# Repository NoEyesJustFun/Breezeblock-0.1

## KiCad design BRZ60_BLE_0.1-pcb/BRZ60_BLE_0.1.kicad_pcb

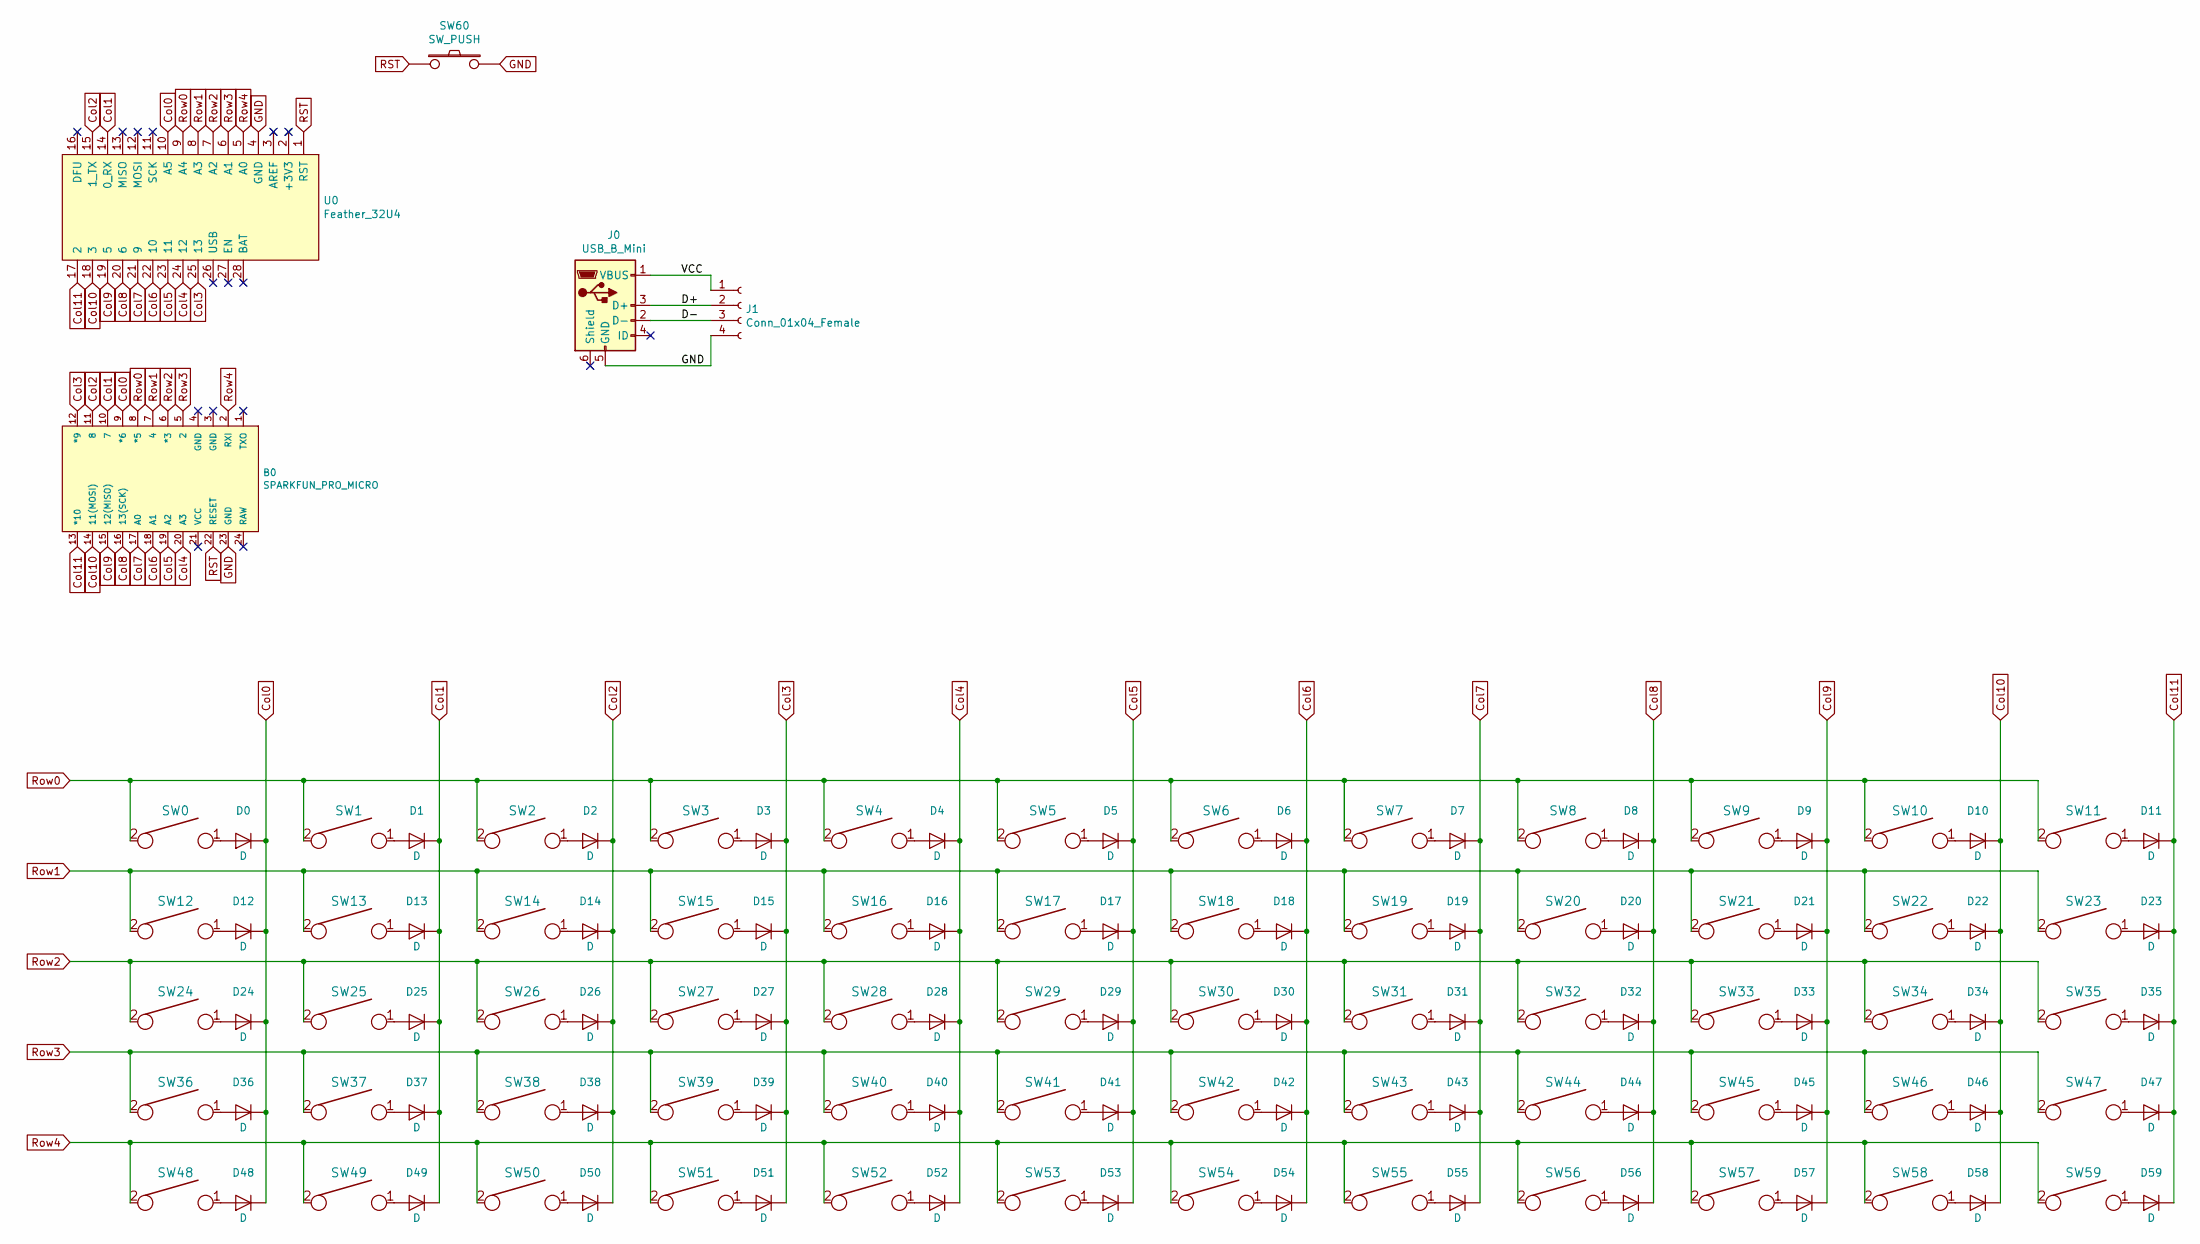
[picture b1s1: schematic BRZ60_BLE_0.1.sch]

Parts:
B0: SPARKFUN_PRO_MICRO; ArduinoProMicro
D0, D1, D2, D3, D4, D5, D6, D7, D8, D9, D10, D11, D12, D13, D14, D15, D16, D17, D18, D19, D20, D21, D22, D23, D24, D25, D26, D27, D28, D29, D30, D31, D32, D33, D34, D35, D36, D37, D38, D39, D40, D41, D42, D43, D44, D45, D46, D47, D48, D49, D50, D51, D52, D53, D54, D55, D56, D57, D58, D59: D; Diode-Hybrid-Back
J0: USB_B_Mini; USB-Mini-B_ LCSC-C46398
J1: Conn_01x04_Female; PinSocket_1x04_P2.00mm_Vertical
SW0, SW1, SW2, SW3, SW4, SW5, SW6, SW7, SW8, SW9, SW10, SW11, SW12, SW13, SW14, SW15, SW16, SW17, SW18, SW19, SW20, SW21, SW22, SW23, SW24, SW25, SW26, SW27, SW28, SW29, SW30, SW31, SW32, SW33, SW34, SW35, SW36, SW37, SW38, SW39, SW40, SW41, SW42, SW43, SW44, SW45, SW46, SW47, SW48, SW49, SW50, SW51, SW52, SW53, SW54, SW55, SW56, SW57, SW58, SW59: KEYSW; MX-Alps-Choc-1U-NoLED
SW60: SW_PUSH; SW_SPST_TL3342
U0: Feather_32U4; PCB_FeatherWing

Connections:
/D+: J0.3 (D+), J1.2
/D-: J0.2 (D-), J1.3
/VCC: J0.1 (VBUS), J1.1
Col0: B0.9 (*6), D0.1 (K), D12.1 (K), D24.1 (K), D36.1 (K), D48.1 (K), U0.10 (A5)
Col1: B0.10 (7), D1.1 (K), D13.1 (K), D25.1 (K), D37.1 (K), D49.1 (K), U0.14 (0_RX)
Col2: B0.11 (8), D2.1 (K), D14.1 (K), D26.1 (K), D38.1 (K), D50.1 (K), U0.15 (1_TX)
Col3: B0.12 (*9), D3.1 (K), D15.1 (K), D27.1 (K), D39.1 (K), D51.1 (K), U0.25 (13)
Col4: B0.20 (A3), D4.1 (K), D16.1 (K), D28.1 (K), D40.1 (K), D52.1 (K), U0.24 (12)
Col5: B0.19 (A2), D5.1 (K), D17.1 (K), D29.1 (K), D41.1 (K), D53.1 (K), U0.23 (11)
Col6: B0.18 (A1), D6.1 (K), D18.1 (K), D30.1 (K), D42.1 (K), D54.1 (K), U0.22 (10)
Col7: B0.17 (A0), D7.1 (K), D19.1 (K), D31.1 (K), D43.1 (K), D55.1 (K), U0.21 (9)
Col8: B0.16 (13(SCK)), D8.1 (K), D20.1 (K), D32.1 (K), D44.1 (K), D56.1 (K), U0.20 (6)
Col9: B0.15 (12(MISO)), D9.1 (K), D21.1 (K), D33.1 (K), D45.1 (K), D57.1 (K), U0.19 (5)
Col10: B0.14 (11(MOSI)), D10.1 (K), D22.1 (K), D34.1 (K), D46.1 (K), D58.1 (K), U0.18 (3)
Col11: B0.13 (*10), D11.1 (K), D23.1 (K), D35.1 (K), D47.1 (K), D59.1 (K), U0.17 (2)
GND: B0.23 (GND), J0.5 (GND), J1.4, SW60.2, U0.4 (GND); also elsewhere on the board
unnamed: D0.2 (A), SW0.1
unnamed: D1.2 (A), SW1.1
unnamed: D2.2 (A), SW2.1
unnamed: D3.2 (A), SW3.1
unnamed: D4.2 (A), SW4.1
unnamed: D5.2 (A), SW5.1
unnamed: D6.2 (A), SW6.1
unnamed: D7.2 (A), SW7.1
unnamed: D8.2 (A), SW8.1
unnamed: D9.2 (A), SW9.1
unnamed: D10.2 (A), SW10.1
unnamed: D11.2 (A), SW11.1
unnamed: D12.2 (A), SW12.1
unnamed: D13.2 (A), SW13.1
unnamed: D14.2 (A), SW14.1
unnamed: D15.2 (A), SW15.1
unnamed: D16.2 (A), SW16.1
unnamed: D17.2 (A), SW17.1
unnamed: D18.2 (A), SW18.1
unnamed: D19.2 (A), SW19.1
unnamed: D20.2 (A), SW20.1
unnamed: D21.2 (A), SW21.1
unnamed: D22.2 (A), SW22.1
unnamed: D23.2 (A), SW23.1
unnamed: D24.2 (A), SW24.1
unnamed: D25.2 (A), SW25.1
unnamed: D26.2 (A), SW26.1
unnamed: D27.2 (A), SW27.1
unnamed: D28.2 (A), SW28.1
unnamed: D29.2 (A), SW29.1
unnamed: D30.2 (A), SW30.1
unnamed: D31.2 (A), SW31.1
unnamed: D32.2 (A), SW32.1
unnamed: D33.2 (A), SW33.1
unnamed: D34.2 (A), SW34.1
unnamed: D35.2 (A), SW35.1
unnamed: D36.2 (A), SW36.1
unnamed: D37.2 (A), SW37.1
unnamed: D38.2 (A), SW38.1
unnamed: D39.2 (A), SW39.1
unnamed: D40.2 (A), SW40.1
unnamed: D41.2 (A), SW41.1
unnamed: D42.2 (A), SW42.1
unnamed: D43.2 (A), SW43.1
unnamed: D44.2 (A), SW44.1
unnamed: D45.2 (A), SW45.1
unnamed: D46.2 (A), SW46.1
unnamed: D47.2 (A), SW47.1
unnamed: D48.2 (A), SW48.1
unnamed: D49.2 (A), SW49.1
unnamed: D50.2 (A), SW50.1
unnamed: D51.2 (A), SW51.1
unnamed 73: D52.2 (A), SW52.1; also elsewhere on the board
unnamed 74: D53.2 (A), SW53.1; also elsewhere on the board
unnamed 75: D54.2 (A), SW54.1; also elsewhere on the board
unnamed: D55.2 (A), SW55.1
unnamed: D56.2 (A), SW56.1
unnamed: D57.2 (A), SW57.1
unnamed: D58.2 (A), SW58.1
unnamed: D59.2 (A), SW59.1
RST: B0.22 (RESET), SW60.1, U0.1 (RST); also elsewhere on the board
Row0: B0.8 (*5), SW0.2, SW1.2, SW2.2, SW3.2, SW4.2, SW5.2, SW6.2, SW7.2, SW8.2, SW9.2, SW10.2, SW11.2, U0.9 (A4)
Row1: B0.7 (4), SW12.2, SW13.2, SW14.2, SW15.2, SW16.2, SW17.2, SW18.2, SW19.2, SW20.2, SW21.2, SW22.2, SW23.2, U0.8 (A3)
Row2: B0.6 (*3), SW24.2, SW25.2, SW26.2, SW27.2, SW28.2, SW29.2, SW30.2, SW31.2, SW32.2, SW33.2, SW34.2, SW35.2, U0.7 (A2)
Row3: B0.5 (2), SW36.2, SW37.2, SW38.2, SW39.2, SW40.2, SW41.2, SW42.2, SW43.2, SW44.2, SW45.2, SW46.2, SW47.2, U0.6 (A1)
Row4: B0.2 (RXI), SW48.2, SW49.2, SW50.2, SW51.2, SW52.2, SW53.2, SW54.2, SW55.2, SW56.2, SW57.2, SW58.2, SW59.2, U0.5 (A0); also elsewhere on the board

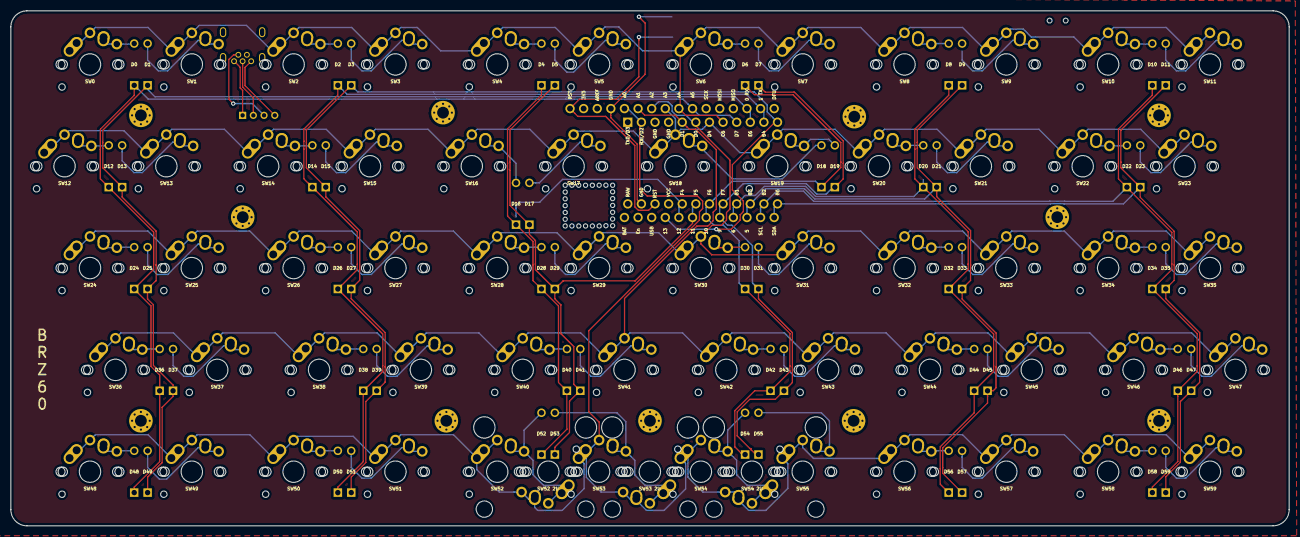
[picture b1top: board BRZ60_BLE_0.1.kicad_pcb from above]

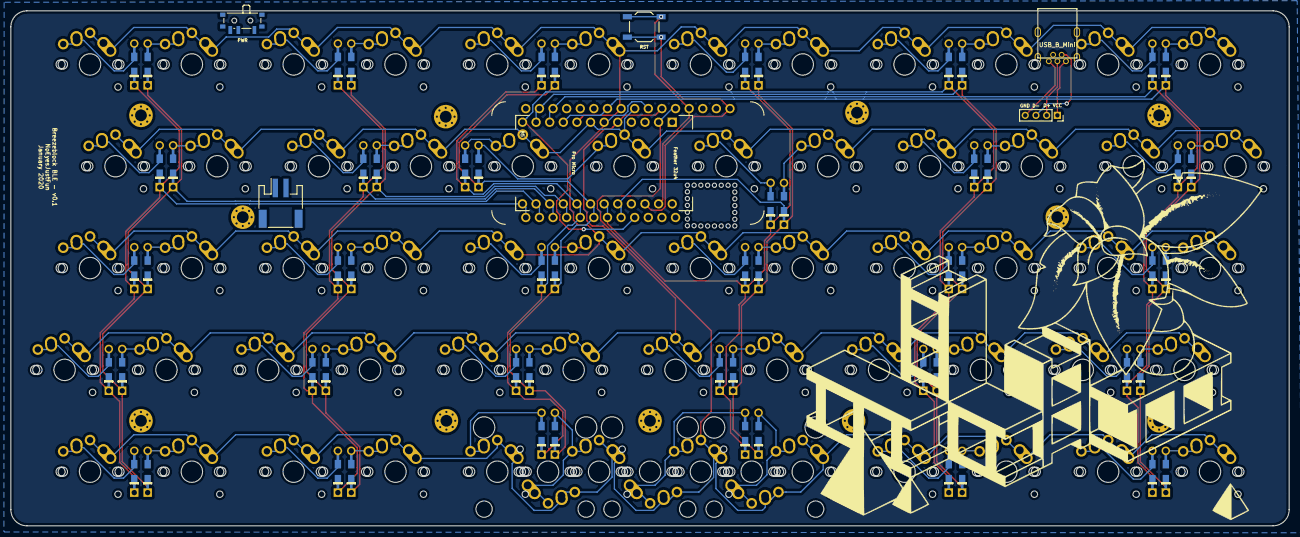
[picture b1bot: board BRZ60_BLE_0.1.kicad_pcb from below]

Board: 2 copper layers, 238.6 x 96.1 mm, 130 parts (7 on the bottom side), 82 nets.

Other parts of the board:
LiPo Conn: JST_PH_S2B-PH-SM4-TB_02x2.00mm_Angled
PWR: SW_SPDT_PCM12
RST: SW_PUSH; SW_SPST_TL3342
SW52#2: KEYSW; MX-Alps-Choc-1U-NoLED
SW53 2U, SW54 2U: KEYSW; MX-Alps-Choc-2U

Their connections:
GND: RST.2; also elsewhere on the board
unnamed 73: SW52#2.1; also elsewhere on the board
unnamed 74: SW53 2U.1; also elsewhere on the board
unnamed 75: SW54 2U.1; also elsewhere on the board
RST: RST.1; also elsewhere on the board
Row4: SW52#2.2, SW53 2U.2, SW54 2U.2; also elsewhere on the board

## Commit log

2020-05-11 Production Ready
